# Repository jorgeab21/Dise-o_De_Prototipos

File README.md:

# KIDBOX

**Consola portátil para niños de 6 a 10 años, sin internet, con juegos que ejercitan la atención y la tolerancia a la frustración, y con un límite de sesión incorporado.**

Proyecto semestral del curso **IND474 · Diseño y Prototipo para el Desarrollo de Productos Físicos** · Universidad Adolfo Ibáñez, Facultad de Ingeniería y Ciencias · 2026, segundo semestre · Profesor: Sebastián Duarte.

> **Estado (13-oct-2026):** propuesta entregada (Semana 8). Para la Semana 10 están listos los documentos de diseño y el esquemático de la PCB (ERC sin errores); en curso, el layout de la PCB y el prototipo en protoboard.

---

## Carta de presentación

Somos un equipo de cuatro estudiantes de Ingeniería Civil Industrial de la UAI. Este repositorio reúne el trabajo de nuestro proyecto semestral: el diseño y prototipo de **KIDBOX**, un producto físico que nace de una pregunta simple: ¿qué le pueden pasar los padres a su hijo cuando hoy le pasan el celular o la tablet?

Partimos del problema y no de la tecnología. Revisamos estudios sobre el uso de pantallas en la infancia, sobre por qué los padres las entregan y sobre qué tipo de juegos pueden aportar al desarrollo cognitivo. De ahí salió un concepto: una consola cerrada, sin internet ni tienda de aplicaciones, con pocos juegos elegidos por su objetivo y con un límite de tiempo que pone la propia consola, no el adulto.

A lo largo del semestre vamos a llevar ese concepto a un prototipo funcional que integra electrónica (PCB propia), programación (firmware y juegos) y diseño mecánico (carcasa impresa en 3D), y lo vamos a probar con niños y padres reales. Aquí documentamos cada etapa: lo que investigamos, lo que decidimos y por qué.

## Equipo

| Integrante | GitHub |
| :-- | :-- |
| Jorge Becerra | [jorgeab21](https://github.com/jorgeab21) |
| Benjamín Fernández | [benjafer38](https://github.com/benjafer38) |
| Adrián Medina | — |
| Daniel Pizarro | [DanielPizarroJ](https://github.com/DanielPizarroJ) |

---

## Problemas identificados

### 1. El problema de las familias

Los padres entregan el celular o la tablet para ocupar o calmar al niño, se sienten culpables al hacerlo y después no pueden limitar su uso sin conflicto.

| Dato | Fuente |
| :-- | :-- |
| El tiempo de juego en niños de 0 a 8 años creció 65 % entre 2020 y 2024. Los de 0 a 8 años pasan 2 h 27 min diarias frente a pantallas. | Common Sense Media, 2025 |
| En Chile, la edad promedio de primer uso es 7,2 años y la del primer celular propio, 9,7 años. | ClaroVTR y Criteria, 2025 |
| El 59,7 % de los cuidadores de niños de 0 a 6 años cree que lo ideal sería que no usaran dispositivos móviles, pero solo el 33,3 % de los niños no los usa en días sin jardín. | Centro UC de la Familia, 2025 |
| El 66 % de los padres usa pantallas para mantener ocupado al niño y el 25 % para calmarlo cuando está enojado. | Common Sense Media, 2025 |
| El 42 % de los padres siente que podría manejar mejor el tiempo de pantalla de sus hijos. | Pew Research Center, 2025 |

La exposición temprana se asocia con retrasos de comunicación y con más rabia y desregulación emocional (Takahashi 2023, Fitzpatrick 2024, Radesky 2022). Son estudios de asociación, no de causalidad. El detalle y las 16 referencias están en [KIDBOX.md](Documentacion/KIDBOX.md).

**Necesidad:** los padres necesitan que sus hijos se entretengan de forma autónoma por periodos cortos, sin contenido inapropiado ni diseños que capturan la atención, y sin tener que ser ellos quienes impongan el límite.

### 2. Usuario y cliente

- **Usuario:** niños y niñas de 6 a 10 años. Es la edad en que empieza el uso habitual de dispositivos y aún no llega el celular propio, y corresponde a la etapa de operaciones concretas de Piaget. El rango se validará en las pruebas con usuarios.
- **Cliente:** madres, padres y cuidadores. Quien compra no es quien usa.

### 3. Desafíos técnicos detectados en la factibilidad

- El parlante disponible en el DEC (CEET120B085) es de 12 V, así que no sirve como parlante definitivo.
- No se puede conectar la batería LiPo directo al microcontrolador: hay que resolver carga y regulación según la placa exacta que se use.
- No hay un D-pad listo en el inventario. Para el prototipo se resuelve con 4 tact switches y una pieza impresa en 3D.
- La PCB de referencia (ESP32-Emu-Turbo) es de 4 capas con componentes SMD, un nivel de complejidad que hay que contrastar con el calendario del curso.

El análisis completo está en [Ideación de Conceptos y factibilidad.pdf](Documentacion/Ideación%20de%20Conceptos%20y%20factibilidad.pdf).

---

## Nuestra propuesta

### Concepto

- **Dispositivo cerrado:** sin WiFi, sin tienda de aplicaciones, sin video ni publicidad.
- **Controles físicos** (cruceta y botones) en lugar de pantalla táctil, para evitar la lógica del scroll.
- **Biblioteca de 3 a 4 juegos**, cada uno con un objetivo: atención sostenida, planificación y memoria de trabajo.
- **Sesiones de 15 a 30 minutos** con aviso previo y cierre automático. La consola pone el límite, no el adulto.
- **Diseño que acompaña la frustración:** deshacer, pistas y dificultad adaptativa, sin cronómetro ni pantalla de game over.
- **Sin mecánicas de retención:** sin rachas, recompensas variables ni reproducción automática.

KIDBOX no se presenta como herramienta para calmar al niño en una crisis, ni como un producto que "mejora la concentración". Se presenta como un producto diseñado a partir de la evidencia, cuyo efecto mediremos en las pruebas con usuarios.

### Diferenciación

No encontramos en el mercado chileno un dispositivo que combine las cuatro características de KIDBOX.

| Producto | Juego | Objetivo cognitivo o emocional | Sin internet abierto | Dispositivo propio |
| :-- | :-: | :-: | :-: | :-: |
| SoyMomo Reloj | No | No | Sí | Sí |
| SoyMomo Tablet Pro 2.0 | Sí, apps de terceros | Parcial | No | Sí |
| PleIQ | Sí | Sí | No | No |
| Tonies / Yoto | No, solo audio | No | Sí | Sí |
| LeapFrog / VTech | Sí | Solo académico | Sí | Sí |
| **KIDBOX** | **Sí** | **Sí** | **Sí** | **Sí** |

### Cómo lo vamos a construir

| Área | Propuesta |
| :-- | :-- |
| Interacción | Táctil (cruceta y botones), visual (pantalla a color) y auditiva (efectos y aviso de fin de sesión). |
| Hardware | Microcontrolador Waveshare RP2350-Plus, pantalla TFT ILI9341 de 2.4", 9 botones, DAC de audio con salida para audífonos, batería con carga USB-C y PCB propia. |
| Software | Firmware con menú, temporizador de sesión y biblioteca de 3 a 4 juegos con dificultad adaptativa. |
| Carcasa | Impresa en 3D, pensada para manos de niños de 6 a 10 años. |

**Base técnica.** Entre dos proyectos open source evaluados elegimos **[ESP32-Emu-Turbo](https://github.com/pjcau/esp32-emu-turbo)** (Concepto A), porque documenta las tres áreas que exige el curso (PCB, firmware y carcasa) y su hardware ya fue validado físicamente. Descartamos **[Cihaz Console](https://github.com/aid-buildandlearn/Cihaz-Console)** (Concepto B) porque usa componentes que no tenemos y tiene la microSD deshabilitada en el firmware. Dada la complejidad de la placa de referencia, estamos evaluando una versión simplificada de la PCB para el prototipo.

**Actualización (13-oct, con el profesor).** Para simplificar la PCB, la base técnica pasó a ser **[Game★Mite](https://github.com/thwill1000/mmbasic-gamemite)** (CC BY 4.0): una placa portadora de módulos, de 2 capas y toda con componentes THT, con una Waveshare RP2350-Plus (que trae cargador de batería), una pantalla ILI9341 de 2.4", un DAC de audio con salida para audífonos (sin parlante) y formato horizontal. El diseño de la PCB está en [`hardware/`](hardware/).

**Fuentes de juegos.** [Simon Tatham's Portable Puzzle Collection](https://www.chiark.greenend.org.uk/~sgtatham/puzzles/) (MIT, puzzles con deshacer y pistas), juegos open source de Game Boy como Tobu Tobu Girl Deluxe, 2048-gb y Petris, y [GCompris](https://gcompris.net/) (KDE, AGPL) como fuente de mecánicas de memoria, lógica y secuencias.

---

## Índice del trabajo

### Entregas

| Semana | Fecha | Entrega | Documentos |
| :-- | :-- | :-- | :-- |
| 8 | 2 oct 2026 | Propuesta del proyecto, ideación y factibilidad (Concepto A vs. B) y BOM preliminar | [KIDBOX.md](Documentacion/KIDBOX.md) · [Documentacion KIDBOX.pdf](Documentacion/Documentacion%20KIDBOX.pdf) · [Ideación de Conceptos y factibilidad.pdf](Documentacion/Ideación%20de%20Conceptos%20y%20factibilidad.pdf) (el BOM preliminar fue reemplazado por la lista de la Semana 10) |
| 10 | 16 oct 2026 | Requisitos, bocetos, BOM, arquitectura HW/SW, PCB/Gerber y plan de desarrollo | [1. Requisitos](1.KIDBOX_Requisitos_y_Requerimientos_Tecnicos.md) · [2. Bocetos](2.KIDBOX_Diagramas_Bocetos_Diseno_Fisico.md) · [3. Componentes](3.KIDBOX_Lista_componentes_electrónicos.md) · [4. Arquitectura](4.KIDBOX_Diagrama_arquitectura_del_Sistema.md) · [5. PCB](hardware/) *(esquemático listo; layout y Gerbers en curso)* · [6. Plan](6.KIDBOX_Plan_de_Desarrollo.md) |
| 12 | 30 oct 2026 | Prototipo en desarrollo | *Pendiente* |
| 13 | 6 nov 2026 | Pruebas con usuarios | *Pendiente* |
| 14 | 13 nov 2026 | Entrega final y presentación | *Pendiente* |

### Documentos del repositorio

| Documento | Contenido |
| :-- | :-- |
| [1.KIDBOX_Requisitos_y_Requerimientos_Tecnicos.md](1.KIDBOX_Requisitos_y_Requerimientos_Tecnicos.md) | Requisitos funcionales, requerimientos técnicos y metas físicas. |
| [2.KIDBOX_Diagramas_Bocetos_Diseno_Fisico.md](2.KIDBOX_Diagramas_Bocetos_Diseno_Fisico.md) | Distribución de controles, boceto de la consola, corte lateral y consideraciones mecánicas. |
| [3.KIDBOX_Lista_componentes_electrónicos.md](3.KIDBOX_Lista_componentes_electrónicos.md) | Lista de componentes del producto (BOM), criterio de batería y estado de cada pieza. |
| [4.KIDBOX_Diagrama_arquitectura_del_Sistema.md](4.KIDBOX_Diagrama_arquitectura_del_Sistema.md) | Arquitectura de hardware y software, asignación de pines y flujo del firmware. |
| [6.KIDBOX_Plan_de_Desarrollo.md](6.KIDBOX_Plan_de_Desarrollo.md) | Cronograma hasta la entrega final y matriz de riesgos. |
| [`hardware/`](hardware/) | Diseño de la PCB: especificación, esquemático KiCad, BOM de la PCB, netlist, layout propuesto y hojas de datos. |
| [Documentacion/KIDBOX.md](Documentacion/KIDBOX.md) | Propuesta completa: problema, usuario, concepto, evidencia, mercado y 16 referencias. |
| [Documentacion/Ideación de Conceptos y factibilidad.pdf](Documentacion/Ideación%20de%20Conceptos%20y%20factibilidad.pdf) | Comparación de los Conceptos A y B, faltantes y justificación de la elección. |
| [Documentacion/Documentacion KIDBOX.pdf](Documentacion/Documentacion%20KIDBOX.pdf) | Propuesta en PDF (entrega Semana 8). |
| [Documentacion/Componentes_DEC_UAI.xlsx](Documentacion/Componentes_DEC_UAI.xlsx) | Inventario de componentes disponibles en el DEC UAI. |
| `Documentacion/01 Problema - Pantallas en niños/` | Uso de pantallas en la infancia (Common Sense Media, Radiografía Digital). |
| `Documentacion/02 Padres - Por qué entregan pantallas/` | Motivos de los padres (Pew, Centro UC de la Familia, estudios cualitativos). |
| `Documentacion/03 Videojuegos y desarrollo cognitivo/` | Evidencia sobre videojuegos y desarrollo (Kollins, Ducharme, Sauce, Siegler, Piaget). |

---

## Evaluación del curso

Tres entregas de avance (25 %, 35 % y 40 % de la nota de entregas) y una presentación final con un prototipo original. La nota final es `NF = NP × 0,7 + PF × 0,3`.

## Nota sobre los documentos

La carpeta `Documentacion/` contiene artículos e informes de terceros usados como respaldo de la propuesta, y pertenecen a sus autores y editoriales. Los datos citados están referenciados en [KIDBOX.md](Documentacion/KIDBOX.md).

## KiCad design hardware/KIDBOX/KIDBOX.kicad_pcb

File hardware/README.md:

# KIDBOX — PCB v1.0

> ## Versión de fabricación v1.0 (27-oct-2026)
> Los Gerbers de `fabricacion/KIDBOX_gerbers_v1.0.zip` son la versión para pedir a JLCPCB. Aprobada en la revisión 2 del profesor
> (26-oct), con las pistas a 45° y la prueba 1:1 de la 150 × 70 hecha el 27-oct.
>
> **Cerrado antes de fabricar:**
> - [x] **Prueba 1:1 de la 150 × 70 (27-oct):** escala confirmada con regla. Pantalla, DAC (jack centrado, boca al borde), pulsadores, C3,
>       C4, RP2350-Plus, batería y SW10 calzan. C2 no aparece porque se perdió la pieza (es igual a C3): hay uno de repuesto en
>       `BOM_compra.csv`. Fotos en "Prueba 1:1".
> - [x] **Pistas a 45°:** las 33 esquinas a 90° pasaron a chaflanes; `verificar_extra.py` cuenta 0 esquinas a 90°.
> - [x] **Medidas del DAC (23–26 oct):** placa 31.85 × 17.5 mm (17.3–17.5), columna a 1.5 mm del borde corto y centrada, eje del jack a
>       24.9 mm de la columna, jack de 4.7 × 14 mm que sobresale 1.4 mm. Ya están en la huella propia de J5.
> - [x] **DAC con 3V3 (23-oct):** VIN = 3.26 V, A3V3 = 3.27 V, suena en estéreo con audífonos. Puentes: venían abiertos; en este módulo
>       **H3L controla FMT y H4L controla XSMT**. Quedaron FLT/DEMP/FMT = L y **XSMT = H** (3.21 V). VIN se queda en 3V3.
> - [x] **RP2350-Plus:** 21.0 × 51.55 mm y filas a 17.78 mm (confirmado).
> - [x] **Continuidad de SW10 (21-oct):** la palanca une el común con la pata de su lado. OFF = pad conectado a GND.
> - [x] **Condensadores medidos (21-oct):** C2/C3 con paso de 5 mm; C4 de Ø ≈ 4 mm, alto 7–8 mm y paso 1.5 mm (huella P1.50).
>
> **Pendientes de después de la placa** (no la cambian):
> - [ ] **Al soldar J2, revisar con lupa los cruces entre pines:** **LRCK–RUN** (entre J2.29 y J2.30) y **3V3–RUN** (entre J2.30 y J2.31).
>       Un puente ahí reinicia el módulo. Ver "Notas de montaje".
> - [ ] **SW10:** medir en ON y OFF (3V3_EN ≈ VSYS / 0 V) y la corriente de la batería en OFF (esperable del orden de decenas de µA; si
>       pasa de ≈ 1 mA algo queda alimentado). Sugerencia del profesor 3.5.
> - [ ] **TP1–TP2:** ≈ 3.3 V con SW10 en ON; sin continuidad con la placa armada sin módulos.
> - [ ] **Carcasa:** muro colgante entre pantalla y DAC, y bolsillo de la batería (ver "Carcasa").
> - [ ] **Alto real del jack** sobre la placa del DAC (hoy ≈ 6 mm, provisorio): define la abertura de la carcasa, no la placa.
> - [ ] **Polaridad del adaptador de la batería** (lo hace el profesor): medir con el multímetro antes de conectar (rojo = + → ⊕ del BAT).
> - [ ] Pantalla: revisar el puente J1 del módulo (3.3 V). No afecta a la PCB.

## Qué es

Consola portátil educativa basada en el **Game★Mite v1.3.2 de Thomas Hugo Williams (CC BY 4.0)**. Placa de **150 × 70 mm**, 2 capas,
todo THT, **simétrica respecto de x = 75**. Lleva:
- un **Waveshare RP2350-Plus** (J1/J2, por detrás, centrado, con el USB-C en el borde superior);
- una **pantalla TFT ILI9341 de 2.4"** por SPI (J3, por delante), con la **imagen** centrada en la placa (`tft.setRotation(3)`);
- un **DAC PCM5102A (GY-PCM5102)** por I2S (J5, **por delante**, bajo la pantalla), con el **jack de 3.5 mm centrado** en el borde inferior;
- **8 pulsadores** con capuchones redondos de Ø9: cruceta a la izquierda, A y B en espejo a la derecha, SELECT y START abajo;
- un **interruptor ON/OFF** (SW10, por detrás, arriba a la izquierda) que corta 3V3_EN;
- **TP1 (+3V3) y TP2 (GND)**, puntos de prueba junto a C2;
- una **batería LiPo 103450** que va en un bolsillo de la **carcasa**, detrás, no pegada a la PCB (ver "Carcasa"). Está en el esquemático
  como BT1, excluida de la placa.

Volumen por software, con máximo limitado.

**Referencias que faltan:** no hay C1, J4 ni SW9 porque se eliminaron en la v0.7 (RESET del frente y conector de la pantalla). No se
re-anotó para no cambiar referencias que ya están en la documentación y en las fotos.

## Archivos

La carpeta de entrega (`KIDBOX_PCB_v1.0/`, la arma `scripts/gen_entrega.py`) tiene la misma estructura que el repositorio:

| Ruta | Qué es |
| :--- | :--- |
| `README.md` | Este archivo |
| `ESPECIFICACION.md` | Fuente de verdad del proyecto (la escribe el alumno), v1.0 |
| `DECISIONES.md` | Supuestos y decisiones del diseño, fase por fase (la v0.9 está en las secciones 16 y 17; la v1.0, en la 18) |
| `KIDBOX/` | Proyecto KiCad 10: `KIDBOX.kicad_pro`, `.kicad_sch`, `.kicad_pcb`, `.kicad_dru` (reglas de 0.29 mm), `fp-lib-table` y `KIDBOX.pretty/` (huella propia del DAC) |
| `KIDBOX/BOM.csv` | Lista de materiales del esquemático (referencia, valor, huella, cara, notas) |
| `KIDBOX/BOM_compra.csv` | **Lista de compra completa**: módulos, batería, tiras, pulsadores, capuchones, tornillos, sujeción de la batería y la placa, con cantidades, estado y proveedor (o "por cotizar") |
| `KIDBOX/netlist.csv` | Red, componente, pin y función de cada pin |
| `KIDBOX/verificacion/` | ERC/DRC en JSON, estadísticas, esquemático en SVG, cobre frontal y trasero (SVG), vistas 3D (PNG) y fotos de las pruebas 1:1 |
| `scripts/` | Generadores (huella del DAC, esquemático, BOM/netlist, PCB, fabricación, entrega) y verificaciones; cada uno dice cómo se ejecuta en su cabecera |
| `fabricacion/KIDBOX_gerbers_v1.0.zip` | **Lo que se sube a JLCPCB:** Gerbers + taladros Excellon |
| `fabricacion/gerbers/` | Los mismos archivos sueltos, más los mapas de taladros (PDF) y el reporte de taladros |
| `fabricacion/KIDBOX_1a1_frente_A4.pdf`, `KIDBOX_1a1_reverso_A4.pdf` | Frente y reverso (espejado) a escala real en hoja A4, para la prueba de impresión |
| `fabricacion/KIDBOX_1a1_frente_Carta.pdf`, `KIDBOX_1a1_reverso_Carta.pdf` | Lo mismo en hoja Carta |

Para regenerar todo desde cero (con KiCad cerrado), desde la carpeta raíz:

```
python scripts/gen_huella_dac.py
python scripts/gen_esquematico.py
python scripts/gen_bom_netlist.py
"C:\Program Files\KiCad\10.0\bin\python.exe" scripts/gen_pcb.py
python scripts/verificar.py KIDBOX
"C:\Program Files\KiCad\10.0\bin\python.exe" scripts/verificar_extra.py KIDBOX
python scripts/gen_fabricacion.py
python scripts/gen_entrega.py
```

## Prueba 1:1 (27-oct-2026)

Hecha con `fabricacion/KIDBOX_1a1_frente_A4.pdf` y `KIDBOX_1a1_reverso_A4.pdf` impresos al 100 % (la serigrafía de las fotos todavía dice
v0.9: la geometría es la misma de la v1.0, que solo cambió las esquinas de las pistas y el número de versión).

| Foto | Qué muestra |
| :--- | :--- |
| `KIDBOX/verificacion/prueba_1a1_v09_escala_largo.jpg` | Regla sobre el largo: 150 mm |
| `KIDBOX/verificacion/prueba_1a1_v09_escala_alto.jpg` | Regla sobre el alto: 70 mm |
| `KIDBOX/verificacion/prueba_1a1_v09_frente.jpg` | Frente: pantalla, DAC con el jack centrado y la boca en el borde, pulsadores, C3 y C4 (C2 falta: se perdió la pieza) |
| `KIDBOX/verificacion/prueba_1a1_v09_reverso.jpg` | Reverso: RP2350-Plus, batería en su zona de referencia y SW10 |

Las fotos `prueba_1a1_v07_*.jpg` son de la v0.7 y quedan como historial.

## Carcasa: lo que la placa le exige

- **Muro entre la pantalla y el DAC.** En la placa queda una **franja libre de 4.74 mm** en planta, entre el borde inferior del módulo de
  pantalla (y = 46.36) y el contorno del DAC (y = 51.1), a lo ancho del DAC (x 48.6–80.45). En esa franja no hay piezas de la cara Top;
  solo pistas. El muro va **colgado de la tapa frontal**:
  - mide **≈ 2 mm** de ancho y va centrado en y = 48.73 (línea "muro carcasa" en F.Fab);
  - su altura útil va de **9 a 18 mm sobre la PCB**, porque lo que debe tapar es la placa del DAC (≈ 11–18 mm sobre su socket);
  - termina **≥ 4 mm sobre la PCB**. Las soldaduras de J2.21/J2.22 y J1.19/J1.20 (≈ 2 mm de alto) caen dentro de la franja, así que
    **no hay que apoyar el muro sobre ellas**.
- **Batería en la carcasa, no en la PCB.** La LiPo 103450 va en un **bolsillo de la carcasa con fondo de plástico** entre la batería y la
  placa, con una **sujeción propia** (traba o tapa) y un **canal para el cable** hasta el conector BAT del RP2350-Plus. No se pega a la
  PCB. El rectángulo "BATERÍA 103450" de la serigrafía trasera es solo la referencia de dónde queda, con una flecha hacia el conector BAT.
  Ahí no van componentes altos de la cara Bottom, pero sí hay patas THT (las de START), que quedan bajo el fondo del bolsillo.
  **Orientar la batería con el cable hacia el conector BAT** del módulo (como en la foto del reverso), para que el cable sea corto y no
  cruce sobre el módulo.
- **Capuchones redondos Ø9** impresos en 3D: dejan ≥ 1.5 mm de aire a los módulos (el más justo es RIGHT, a 2.41 mm de la pantalla).
- **Aberturas:** USB-C arriba (x 70.7–79.65) y jack abajo (x 72.65–77.35, boca al ras de y = 70, a ≈ 13–19 mm sobre la placa).

## Orden de soldadura

Las piezas de la **cara Bottom** se insertan por detrás y se sueldan por delante. Las de **Top** se insertan por delante y se sueldan
por detrás. Primero va todo Bottom y después Top, de lo más bajo a lo más alto.

| # | Ref | Cara | Pieza | Cuidado |
| :--- | :--- | :--- | :--- | :--- |
| 1 | J1 | Bottom | Tira hembra 1×20 (pines 1–20 del módulo) | Pin 1 = pad cuadrado, junto al USB-C. Cortar al ras |
| 2 | J2 | Bottom | Tira hembra 1×20 (pines 21–40) | **Poco estaño**: por delante pasan entre sus pines el haz SPI, 3V3 y LRCK (ver notas). Cortar al ras |
| 3 | SW10 | Bottom | Interruptor deslizante, paso 2.54 mm | Palanca hacia atrás; pad central = común. Las patas quedan bajo la pantalla: cortar al ras |
| 4 | C2 | Top | 100 nF cerámico (paso 5 mm) | Vertical junto al pin 1 de J3 |
| 5 | C3 | Top | 100 nF cerámico (paso 5 mm) | Vertical entre SELECT y el DAC, encima de C4 |
| 6 | C4 | Top | 10 µF 25 V electrolítico (Ø4 × 7–8 mm, paso 1.5 mm) | **Respetar la polaridad:** + en el pad cuadrado, del lado de J5 (a la derecha visto de frente). La huella ya tiene paso 1.5 mm: no hay que abrir las patas |
| 7 | J3 | Top | Tira hembra 1×14 (pantalla) | Pin 1 (VCC) arriba, marcado "1". Cortar al ras |
| 8 | J5 | Top | Tira hembra 1×6 (DAC) | VIN = pin 1, pad cuadrado, abajo. El DAC va con sus componentes hacia el frente y el jack hacia el borde inferior |
| 9 | SW1–SW8 | Top | Pulsadores 6×6 | Bien apoyados contra la placa para que los capuchones queden a la misma altura |

TP1 y TP2 son pads de la placa: no llevan pieza.

### Notas de montaje
- **J2 con poco estaño.** Entre sus pines pasan, por la cara donde se suelda, todas a 0.295 mm de cada pad:
  - el haz SPI (5 pistas);
  - **3V3**, entre J2.31 (LCD_LED) y J2.30 (RUN);
  - **I2S_LRCK**, entre J2.30 (RUN) y J2.29 (DIN).

  Hay que **revisar con lupa sobre todo los puentes LRCK–RUN y 3V3–RUN**: el primero reiniciaría el módulo cada vez que suena el
  audio, y el segundo dejaría RUN fijo en 3V3 (y LCD_LED en corto con 3V3 si el puente toca J2.31). Medir que no haya continuidad
  entre J2.30 y J2.29, entre J2.30 y J2.31, ni entre 3V3 (TP1) y J2.30 o J2.31.
- **J3 y J5 sin pistas entre sus pines** (v0.9). Se puede soldar normal.
- **DAC adelante:** la tira macho se suelda con el **plástico del lado sin componentes** del módulo. Los componentes del DAC quedan hacia el
  frente y la boca del jack al ras del borde inferior. Bajo el DAC no queda ninguna pata salvo las de J5, así que el módulo también se
  puede soldar directo a la placa para bajar el grosor.
- **Puentes del DAC:** FLT, DEMP y FMT = L; **XSMT = H** (sin él, el DAC queda en silencio). En este módulo H3L controla FMT y H4L controla XSMT.
- **Cortar al ras las patas de J1, J2, J3 y SW10** después de soldar: las de J1/J2 y SW10 quedan bajo la pantalla.
- La placa no tiene vías. La cara de atrás es un plano de masa con alivios térmicos, así que los pads de GND se sueldan igual que los demás.
- Antes de poner los módulos: medir que no haya corto entre **TP1 (3V3) y TP2 (GND)**.
- Firmware: `tft.setRotation(3)`; volumen limitado por software.

## Pedido en JLCPCB

| Parámetro | Valor |
| :--- | :--- |
| Archivo | `fabricacion/KIDBOX_gerbers_v1.0.zip` (extensiones Protel, Gerber X2, taladros Excellon en mm con origen absoluto) |
| Base material | FR-4 |
| Layers | **2** |
| Dimensions | **150 × 70 mm** (lo detecta solo; el sobrecosto por pasar de 100 × 100 mm está aceptado) |
| PCB Qty | 5 (mínimo) |
| Product type | Industrial/Consumer electronics |
| Different design | 1 |
| Delivery format | Single PCB |
| PCB thickness | **1.6 mm** |
| PCB color | **Verde** |
| Silkscreen | Blanco |
| Surface finish | **HASL (with lead free)** |
| Outer copper weight | 1 oz |
| Via covering | Tented (la placa no tiene vías) |
| Mark on PCB / order number | **Order number: Specify a location**: va donde está el texto "JLCJLCJLCJLC" de la serigrafía inferior, dentro de la zona de batería |
| Gold fingers, castellated holes, edge plating | No |
| **PCB Assembly (PCBA)** | **No** (sin ensamblaje) |
| Stencil | No |
| Resto de opciones | Las que JLCPCB trae por defecto |

## Qué revisar en el visor de Gerbers de JLCPCB antes de pagar

1. **2 capas y 150 × 70 mm.** El contorno tiene esquinas redondeadas (r = 4 mm), sin líneas sueltas ni recortes de más.
2. **Taladros: 107 en total.**
   - 103 metalizados: 2 × 0.6 mm (C4), 7 × 0.8 mm (C2, C3 y SW10), 62 × 1.0 mm (J1, J2, J3, J5, TP1 y TP2) y 32 × 1.1 mm (pulsadores).
   - 4 sin metalizar de 2.2 mm, en las esquinas (4, 4), (146, 4), (4, 66) y (146, 66).
   - Dentro del rectángulo "BATERÍA 103450" (por detrás) solo caen las patas de START: la batería va en la carcasa, no sobre la placa.
3. **Cobre superior (Top):** todas las pistas están aquí, con todas las esquinas a 45° (ninguna a 90°). Las de señal son de 0.25 mm y las de 3V3 de 0.5 mm, salvo un tramo de 0.25 mm entre
   dos pines de J2. Ninguna pista toca un pad que no le corresponde. No hay vías.
4. **Cobre inferior (Bottom):** un plano de masa casi completo. Los pads de GND tienen alivios térmicos (4 "radios") y los demás pads,
   un anillo libre a su alrededor. No hay pistas.
5. **Máscara:** hay abertura en todos los pads, y ninguna sobre las pistas ni sobre el plano.
6. **Serigrafía superior:**
   - UP, DOWN, LEFT, RIGHT, A, B, SELECT y START junto a sus botones (texto de 1.2 mm);
   - el contorno de la pantalla con "PANTALLA TFT 2.4" (J3)" y "1" junto al pin 1 de J3, y dentro el contorno de la imagen;
   - el contorno del DAC con el jack, "DAC PCM5102", "VIN" y "GND" junto a J5;
   - "3V3" y "GND" junto a TP1 y TP2;
   - los créditos del Game*Mite entre el DAC y START.
7. **Serigrafía inferior.** En la vista desde arriba se ve espejada, que es lo correcto; al dar vuelta la placa en el visor se lee al derecho:
   - "VISTA POSTERIOR / FILAS ESPEJADAS", el contorno de la RP2350-Plus con el USB-C arriba y "1" en J1 y J2;
   - "OFF" y "ON" en SW10 (desde atrás, arriba a la derecha, con OFF a la izquierda);
   - "BATERÍA 103450 / va en la carcasa, no pegar a la PCB" con una flecha hacia el conector BAT, y el cajetín
     "KIDBOX v1.0 – 150 x 70 mm – 1.6 mm – 2 capas" abajo (a la izquierda al dar vuelta la placa).
8. Ningún texto de serigrafía cae sobre un pad. El DRC dio 0 avisos, pero hay que confirmarlo a la vista.
9. En la serigrafía inferior aparece **"JLCJLCJLCJLC"** en vertical, dentro de la zona de batería, junto a "BATERÍA 103450". Ahí JLCPCB pone su número de pedido (con "Specify a location").
10. Precio y plazo coherentes con 5 placas de 150 × 70 mm, sin ensamblaje ni opciones extra marcadas por error.

## Verificación del diseño (27-oct-2026)

`verificar.py`: ERC 0/0 · DRC 0 errores, 0 avisos (con las reglas de 0.29 mm de `KIDBOX.kicad_dru`) · 0 sin conectar · paridad
esquemático-PCB 0 · mínimos DFM OK.

`verificar_extra.py`:
- ERC y DRC con los tests que el proyecto ignora activados: 0.
- Emulación de "Actualizar PCB desde esquemático" (F8): 0 cambios.
- Esquinas de pista: 115 vértices, 112 a 45° y 3 colineales; **0 a 90°**.

Detalle y holguras medidas en `DECISIONES.md`, secciones 16 a 18.

Licencia y créditos: basado en el Game★Mite de Thomas Hugo Williams (CC BY 4.0).

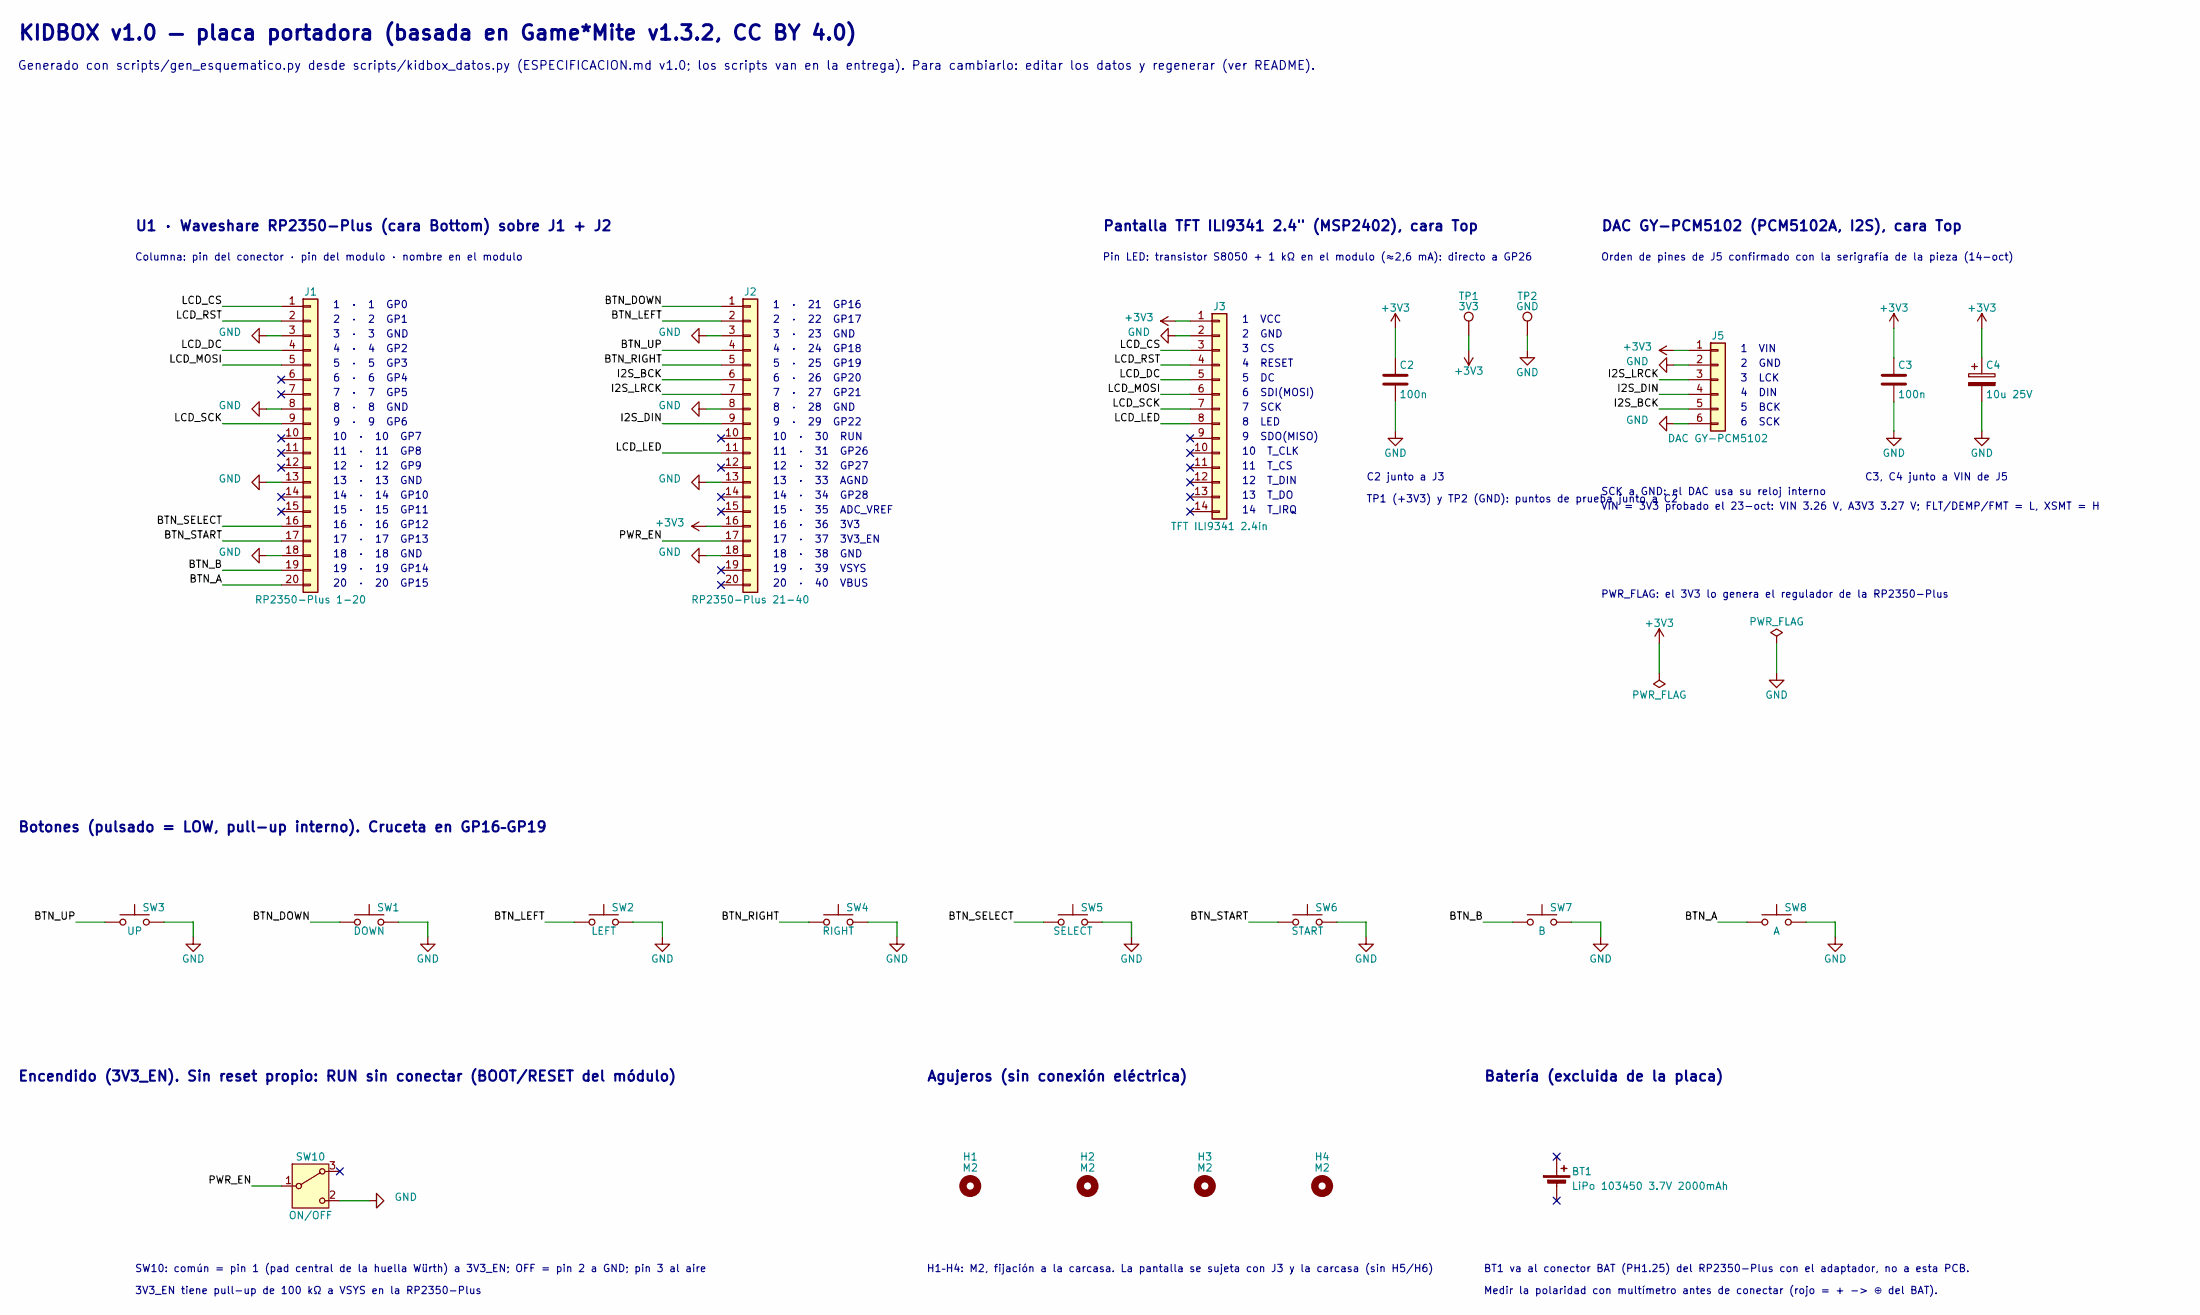
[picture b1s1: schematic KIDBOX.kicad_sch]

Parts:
BT1: LiPo 103450 3.7V 2000mAh
C2, C3: 100n; C_Disc_D5.0mm_W2.5mm_P5.00mm
C4: 10u 25V; CP_Radial_D4.0mm_P1.50mm
H1, H2, H3, H4: M2; MountingHole_2.2mm_M2
J1: RP2350-Plus 1-20; PinSocket_1x20_P2.54mm_Vertical
J2: RP2350-Plus 21-40; PinSocket_1x20_P2.54mm_Vertical
J3: TFT ILI9341 2.4in; PinSocket_1x14_P2.54mm_Vertical
J5: DAC GY-PCM5102; GY-PCM5102_1x06_P2.54mm
SW1: DOWN; SW_PUSH_6mm
SW2: LEFT; SW_PUSH_6mm
SW3: UP; SW_PUSH_6mm
SW4: RIGHT; SW_PUSH_6mm
SW5: SELECT; SW_PUSH_6mm
SW6: START; SW_PUSH_6mm
SW7: B; SW_PUSH_6mm
SW8: A; SW_PUSH_6mm
SW10: ON/OFF; SW_Slide-03_Wuerth-WS-SLTV_10x2.5x6.4_P2.54mm
TP1: 3V3; TestPoint_THTPad_D2.0mm_Drill1.0mm
TP2: GND; TestPoint_THTPad_D2.0mm_Drill1.0mm

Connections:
+3V3: C2.1, C3.1, C4.1, J2.16, J3.1, J5.1, TP1.1
/BTN_A: J1.20, SW8.1
/BTN_B: J1.19, SW7.1
/BTN_DOWN: J2.1, SW1.1
/BTN_LEFT: J2.2, SW2.1
/BTN_RIGHT: J2.5, SW4.1
/BTN_SELECT: J1.16, SW5.1
/BTN_START: J1.17, SW6.1
/BTN_UP: J2.4, SW3.1
/I2S_BCK: J2.6, J5.5
/I2S_DIN: J2.9, J5.4
/I2S_LRCK: J2.7, J5.3
/LCD_CS: J1.1, J3.3
/LCD_DC: J1.4, J3.5
/LCD_LED: J2.11, J3.8
/LCD_MOSI: J1.5, J3.6
/LCD_RST: J1.2, J3.4
/LCD_SCK: J1.9, J3.7
/PWR_EN: J2.17, SW10.1 (B)
GND: C2.2, C3.2, C4.2, J1.3, J1.8, J1.13, J1.18, J2.3, J2.8, J2.13, J2.18, J3.2, J5.2, J5.6, SW1.2, SW2.2, SW3.2, SW4.2, SW5.2, SW6.2, SW7.2, SW8.2, SW10.2 (C), TP2.1

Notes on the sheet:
KIDBOX v1.0 — placa portadora (basada en Game*Mite v1.3.2, CC BY 4.0)
Generado con scripts/gen_esquematico.py desde scripts/kidbox_datos.py (ESPECIFICACION.md v1.0; los scripts van en la entrega). Para cambiarlo: editar los datos y regenerar (ver README).
U1 · Waveshare RP2350-Plus (cara Bottom) sobre J1 + J2
Columna: pin del conector · pin del modulo · nombre en el modulo
1 · 1 GP0
2 · 2 GP1
3 · 3 GND
4 · 4 GP2
5 · 5 GP3
6 · 6 GP4
7 · 7 GP5
8 · 8 GND
9 · 9 GP6
10 · 10 GP7
11 · 11 GP8
12 · 12 GP9
13 · 13 GND
14 · 14 GP10
15 · 15 GP11
16 · 16 GP12
17 · 17 GP13
18 · 18 GND
19 · 19 GP14
20 · 20 GP15
1 · 21 GP16
2 · 22 GP17
3 · 23 GND
4 · 24 GP18
5 · 25 GP19
6 · 26 GP20
7 · 27 GP21
8 · 28 GND
9 · 29 GP22
10 · 30 RUN
11 · 31 GP26
12 · 32 GP27
13 · 33 AGND
14 · 34 GP28
15 · 35 ADC_VREF
16 · 36 3V3

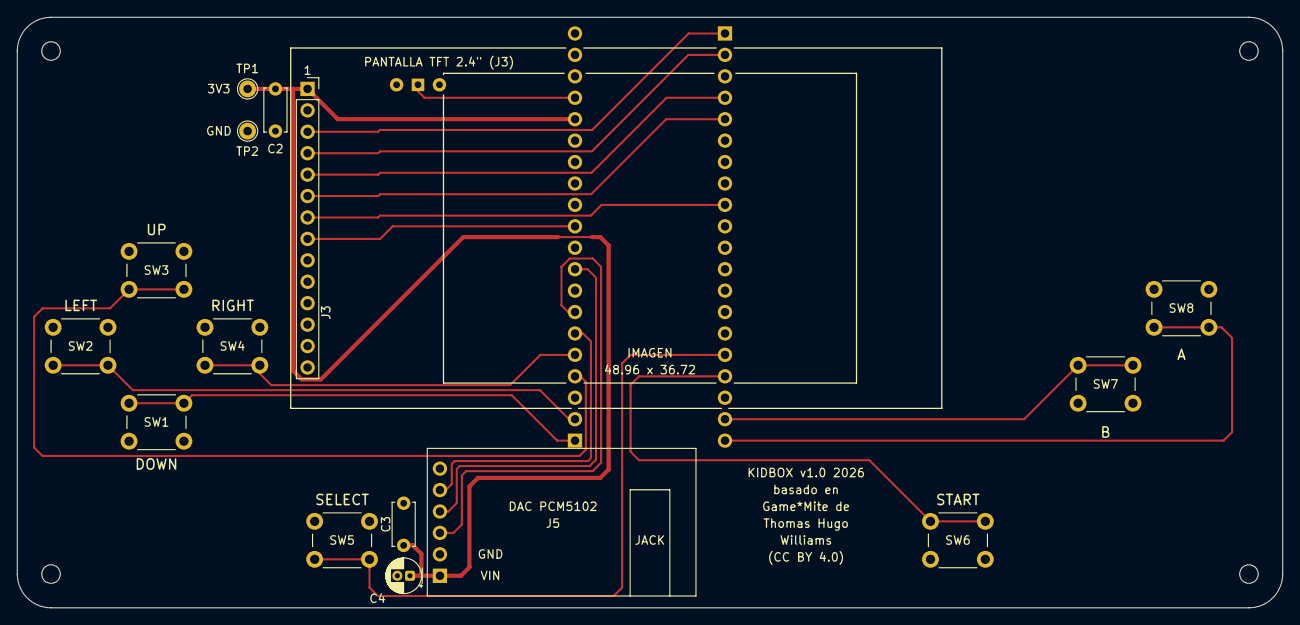
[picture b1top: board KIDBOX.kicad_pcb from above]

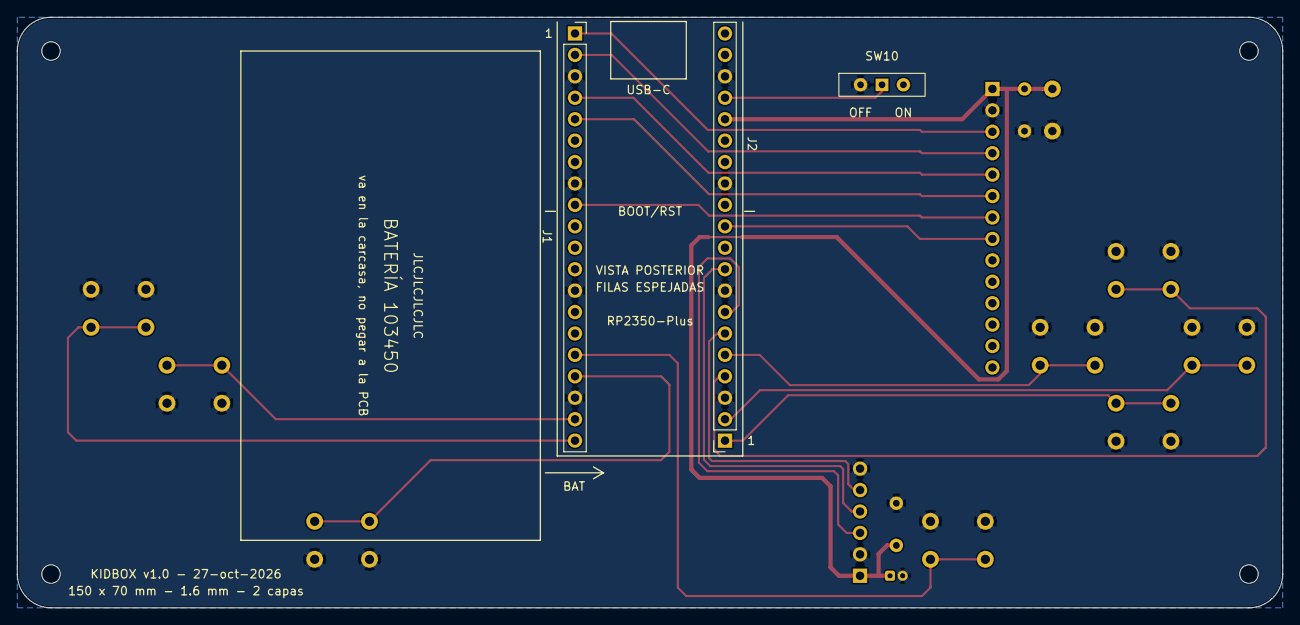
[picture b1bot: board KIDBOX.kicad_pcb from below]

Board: 2 copper layers, 150.0 x 70.0 mm, 22 parts (3 on the bottom side), 20 nets.

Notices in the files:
hardware/KIDBOX/KIDBOX.kicad_pcb:
Basado en Game*Mite v1.3.2 de Thomas Hugo Williams (CC BY 4.0)
